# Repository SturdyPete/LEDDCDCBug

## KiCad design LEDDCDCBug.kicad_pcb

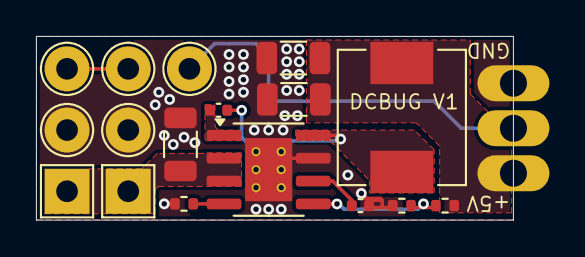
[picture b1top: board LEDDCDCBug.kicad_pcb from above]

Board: 2 copper layers, 26.5 x 10.2 mm, 18 parts (0 on the bottom side), 10 nets.

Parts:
C1: 100nF, 50V; C_0402_1005Metric
C2, C3: 22uF, 6.3V; C_1206_3216Metric
C4: 10nF, 16V; C_0402_1005Metric
C5: 10uF, 50V; C_1206_3216Metric
J1, J4: Conn_01x01; TestPoint_THTPad_2.5x2.5mm_Drill1.2mm
J2, J3, J5, J6, J7: Conn_01x01; TestPoint_THTPad_D2.5mm_Drill1.2mm
J8: Conn_01x01; WS2812 castles
L1: 5.5uH; L_Sunlord_MWSA0603S
R1: 115k, 1%; R_0402_1005Metric
R2: 22k1, 1%; R_0402_1005Metric
R3: 200k, 5%; R_0402_1005Metric
U1: SOIC-8-1EP_3.9x4.9mm_P1.27mm_EP2.62x3.51mm_ThermalVias

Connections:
+36V: C5.2, J1.1, J4.1, U1.2 (VIN), U1.3 (EN)
/+5V: C2.2, C3.2, J8.1, L1.2, R1.1
/BST: C1.1, U1.1 (BST)
/DATA_IN: J3.1, J8.2
/DATA_OUT: J6.1, J7.1
/FB: R1.2, R2.1, U1.5 (FB)
/RT: R3.1, U1.4 (RT/CLK)
/SS: C4.2, U1.6 (SS)
/SW: C1.2, L1.1, U1.8 (SW)
GND: C2.1, C3.1, C4.1, C5.1, J2.1, J5.1, J8.3, R2.2, R3.2, U1.7 (GND), U1.9 (TP)

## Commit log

2025-05-16 update design calcs based on real component data
2025-05-16 add title block
